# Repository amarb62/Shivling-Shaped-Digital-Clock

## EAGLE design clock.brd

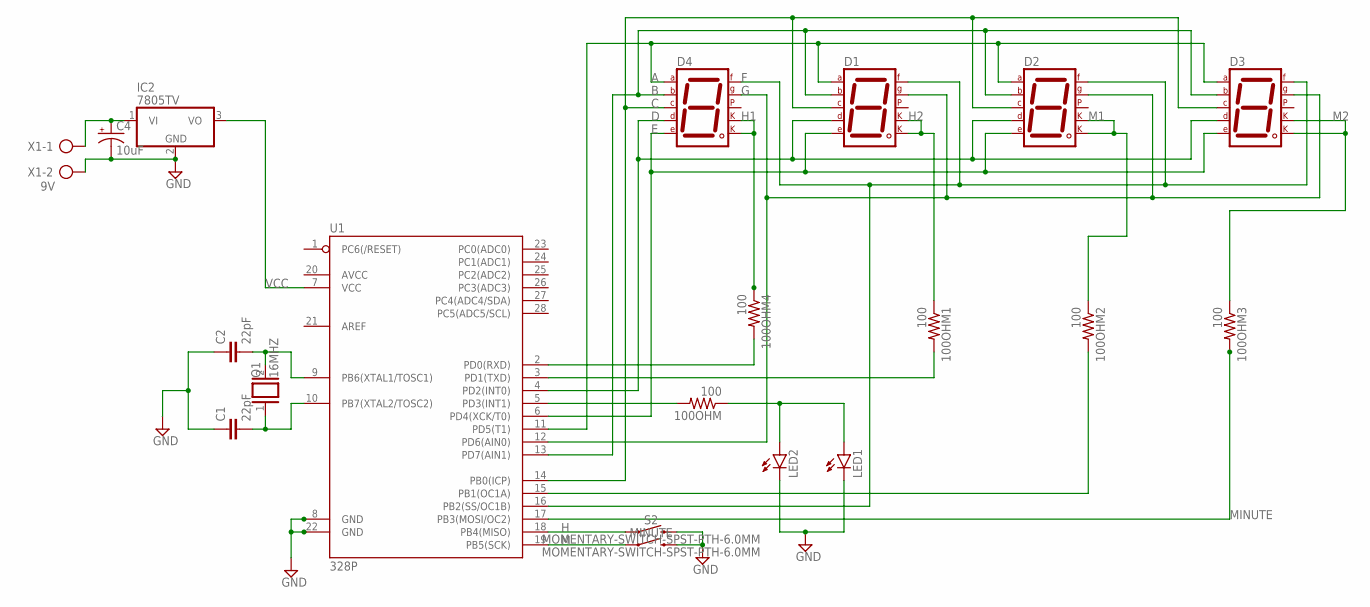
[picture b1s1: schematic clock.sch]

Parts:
100OHM, 100OHM1, 100OHM2, 100OHM3, 100OHM4: 100; 0207/10
C1, C2: 22pF; CAP-PTH-2.54
C4: 10uF; CPOL-RADIAL-2.5MM-5MM
D1, D2, D3, D4: 7SEG-CK; 7SEG-13
IC2: 7805TV; TO220V
LED1, LED2: LED5MM
MINUTE: MOMENTARY-SWITCH-SPST-PTH-6.0MM; TACTILE_SWITCH_PTH_6.0MM
Q1: 16MHZ; QS
S2: MOMENTARY-SWITCH-SPST-PTH-6.0MM; TACTILE_SWITCH_PTH_6.0MM
U1: 328P; DIP28
X1: 9V; AK500/2-H

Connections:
A: D1.7 (A), D2.7 (A), D3.7 (A), D4.7 (A), U1.11 (PD5(T1))
B: D1.6 (B), D2.6 (B), D3.6 (B), D4.6 (B), U1.13 (PD7(AIN1))
C: D1.4 (C), D2.4 (C), D3.4 (C), D4.4 (C), U1.14 (PB0(ICP))
D: D1.2 (D), D2.2 (D), D3.2 (D), D4.2 (D), U1.4 (PD2(INT0))
E: D1.1 (E), D2.1 (E), D3.1 (E), D4.1 (E), U1.6 (PD4(XCK/T0))
F: D1.9 (F), D2.9 (F), D3.9 (F), D4.9 (F), U1.16 (PB2(SS/OC1B))
G: D1.10 (G), D2.10 (G), D3.10 (G), D4.10 (G), U1.12 (PD6(AIN0))
GND: C1.1, C2.1, C4.2 (-), IC2.2 (GND), LED1.K (C), LED2.K (C), MINUTE.3 (2), S2.3 (2), U1.8 (GND), U1.22 (GND), X1.2
H: S2.1, U1.18 (PB4(MISO))
H1: 100OHM4.1, D4.3 (CK1), D4.8 (CK2)
H2: 100OHM1.1, D1.3 (CK1), D1.8 (CK2)
LED: 100OHM.1, LED1.A, LED2.A
M: MINUTE.1, U1.19 (PB5(SCK))
M1: 100OHM2.1, D2.3 (CK1), D2.8 (CK2)
M2: 100OHM3.1, D3.3 (CK1), D3.8 (CK2)
MINUTE: 100OHM3.2, U1.17 (PB3(MOSI/OC2))
unnamed: C2.2, Q1.2, U1.9 (PB6(XTAL1/TOSC1))
unnamed: 100OHM4.2, U1.2 (PD0(RXD))
unnamed: C1.2, Q1.1, U1.10 (PB7(XTAL2/TOSC2))
unnamed: C4.1 (+), IC2.1 (VI), X1.1
unnamed: 100OHM2.2, U1.15 (PB1(OC1A))
unnamed: 100OHM1.2, U1.3 (PD1(TXD))
unnamed: 100OHM.2, U1.5 (PD3(INT1))
VCC: IC2.3 (VO), U1.7 (VCC)

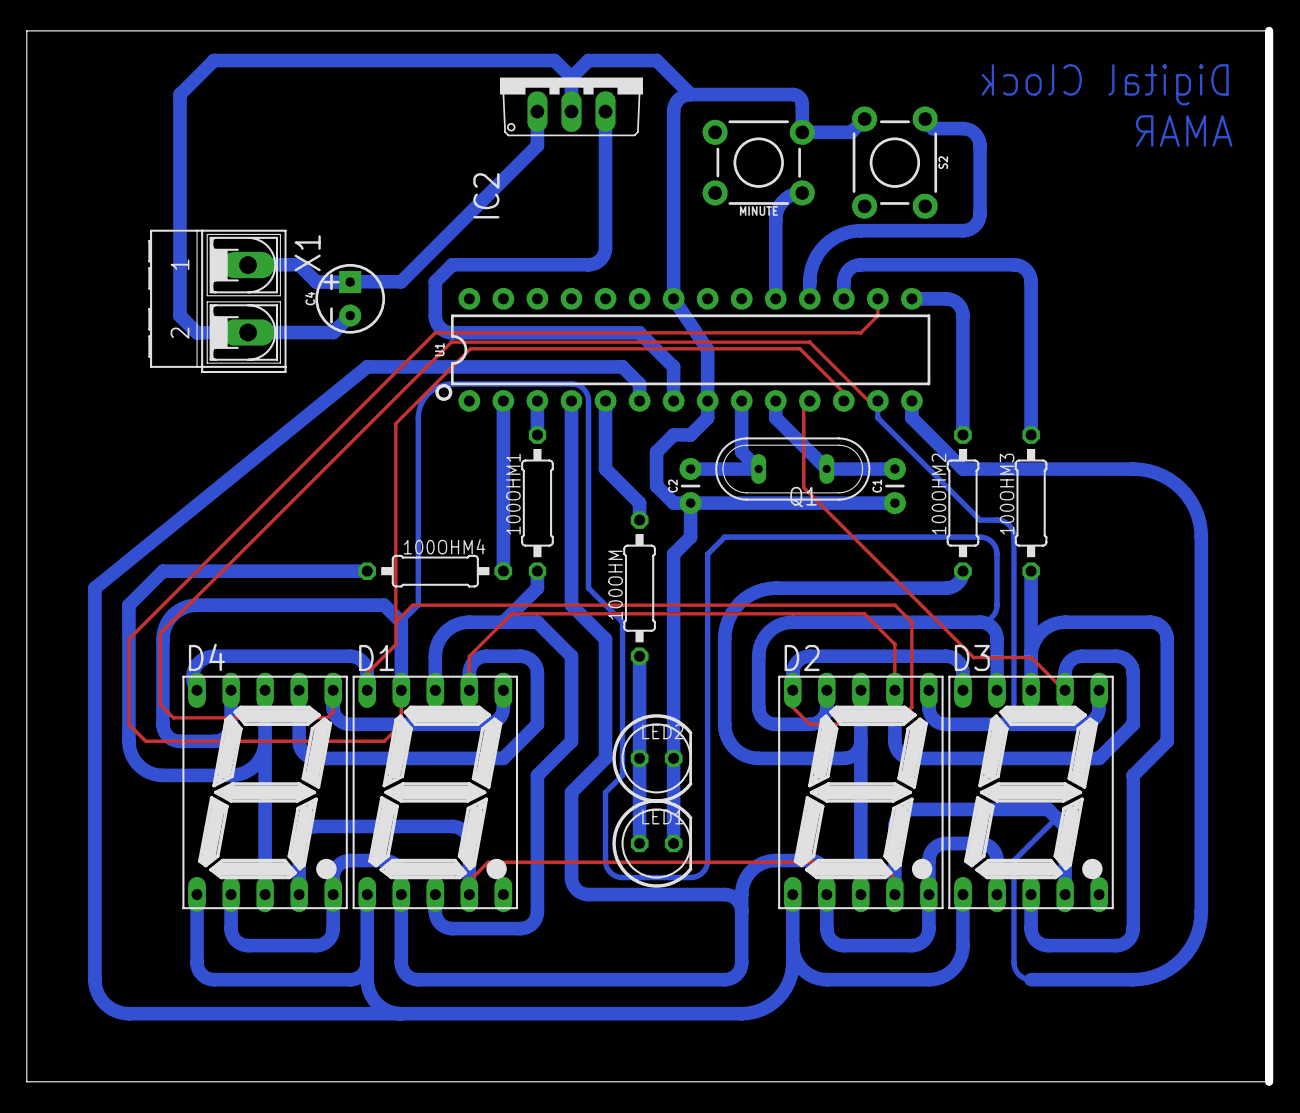
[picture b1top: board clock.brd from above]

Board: 2 copper layers, 92.4 x 78.4 mm, 20 parts (0 on the bottom side), 24 nets.
